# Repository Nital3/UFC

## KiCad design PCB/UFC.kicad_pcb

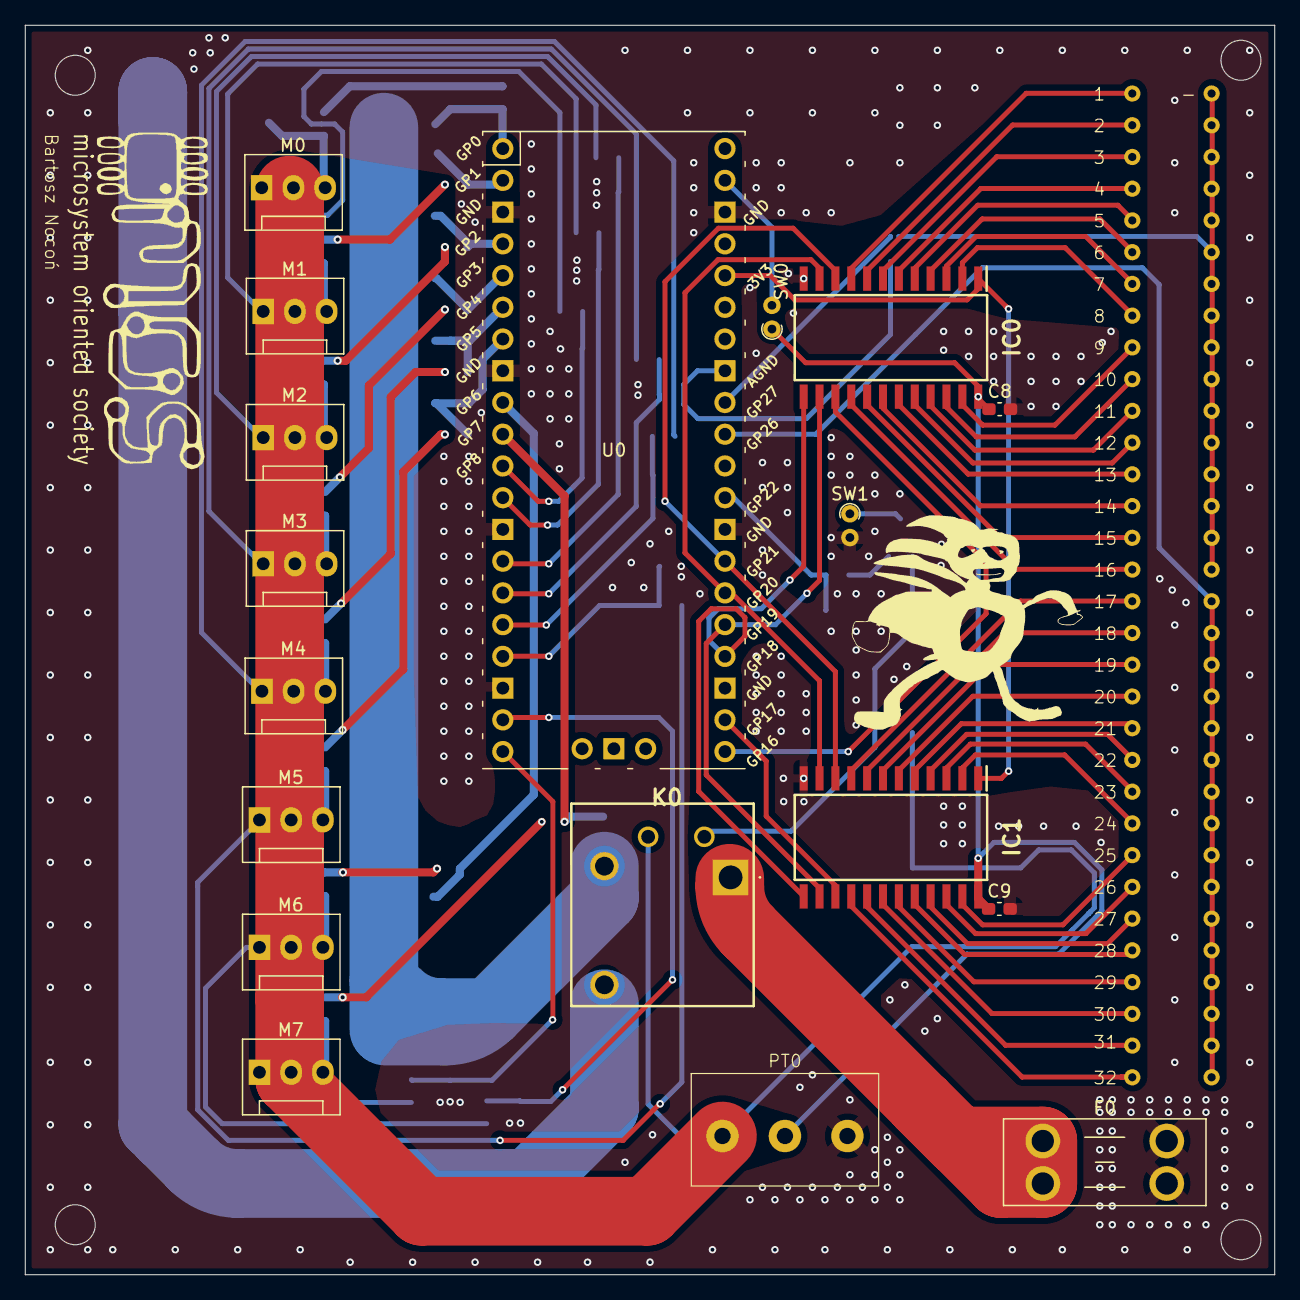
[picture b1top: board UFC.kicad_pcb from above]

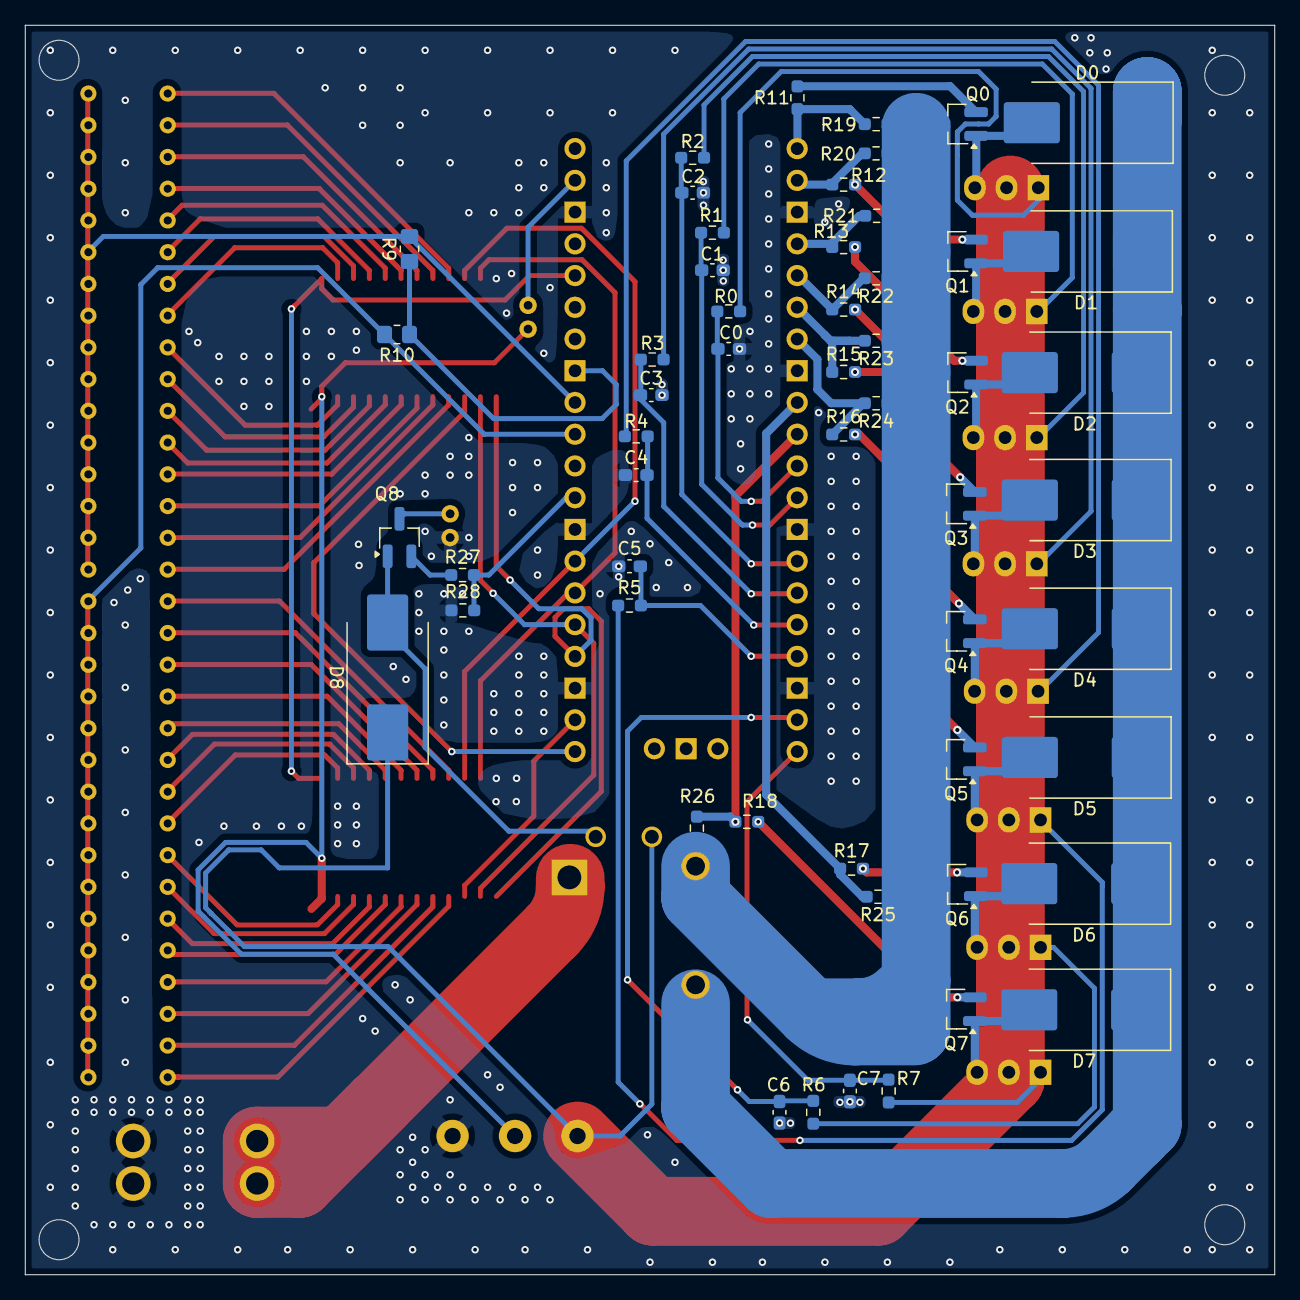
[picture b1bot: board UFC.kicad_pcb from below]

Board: 2 copper layers, 100.0 x 100.0 mm, 73 parts (54 on the bottom side), 85 nets.

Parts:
C0, C1, C2, C3, C4, C5, C6, C7: 4.7u; C_0603_1608Metric_Pad1.08x0.95mm_HandSolder
C8: 1u; C_0603_1608Metric_Pad1.08x0.95mm_HandSolder
C9: C; C_0603_1608Metric_Pad1.08x0.95mm_HandSolder
CONN0: NTC_connector_32x2
D0, D1, D2, D3, D4, D5, D6, D7, D8: D; D_SMC_Handsoldering
F0: Main 12V Fuse; Fuseholder_Blade_Mini_Keystone_3568
IC0, IC1: CD74HCT4067M; SOIC127P1030X265-24N
K0: EP1-3N1S; EP13N1S
M0, M1, M2, M3, M4, M5, M6, M7: Fan_3pin; FanPinHeader_1x03_P2.54mm_Vertical
PT0: Screw_terminal
Q0, Q1, Q2, Q3, Q4, Q5, Q6, Q7, Q8: NMOS; SOT-23_Handsoldering
R0, R1, R2, R3, R4, R5, R6, R7: R300; R_0603_1608Metric_Pad0.98x0.95mm_HandSolder
R9, R10: 10kR; R_0805_2012Metric_Pad1.20x1.40mm_HandSolder
R11, R12, R13, R14, R15, R16, R17, R18, R27: 470R; R_0603_1608Metric_Pad0.98x0.95mm_HandSolder
R19, R20, R21, R22, R23, R24, R25, R26: 4.7KR; R_0603_1608Metric_Pad0.98x0.95mm_HandSolder
R28: R47k; R_0603_1608Metric_Pad0.98x0.95mm_HandSolder
SW0: MCU Reset; R_Axial_DIN0204_L3.6mm_D1.6mm_P1.90mm_Vertical
SW1: Main Power Switch; R_Axial_DIN0204_L3.6mm_D1.6mm_P1.90mm_Vertical
U0: Pico_1; RPi_Pico_TH

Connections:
+5V: C8.1, C9.1, IC0.24 (VCC), IC1.24 (VCC), PT0.2 (5V), SW0.1 (A)
+12V: D8.1 (K), K0.3 (COIL_2), M0.2 (+), M1.2 (+), M2.2 (+), M3.2 (+), M4.2 (+), M5.2 (+), M6.2 (+), M7.2 (+), PT0.1 (12V)
/ADC0: CONN0.17, CONN0.18, CONN0.19, CONN0.20, CONN0.21, CONN0.22, CONN0.23, CONN0.24, CONN0.25, CONN0.26, CONN0.27, CONN0.28, CONN0.29, CONN0.30, CONN0.31, CONN0.32, R9.2, U0.32 (GPIO27_ADC1)
/ADC1: CONN0.49, CONN0.50, CONN0.51, CONN0.52, CONN0.53, CONN0.54, CONN0.55, CONN0.56, CONN0.57, CONN0.58, CONN0.59, CONN0.60, CONN0.61, CONN0.62, CONN0.63, CONN0.64, R10.2, U0.31 (GPIO26_ADC0)
/AGND: R9.1, R10.1, U0.33 (AGND)
/DEMUX 3.3V: IC0.1 (COMMON_INPUT/OUTPUT), IC1.1 (COMMON_INPUT/OUTPUT), U0.36 (3V3)
/DEMUX(0-15)_Disable: IC0.15 (~E), U0.21 (GPIO16)
/DEMUX(16-31)_Disable: IC1.15 (~E), U0.22 (GPIO17)
/DEMUX-Address0: IC0.10 (S0), IC1.10 (S0), U0.27 (GPIO21)
/DEMUX-Address1: IC0.11 (S1), IC1.11 (S1), U0.26 (GPIO20)
/DEMUX-Address2: IC0.14 (S2), IC1.14 (S2), U0.25 (GPIO19)
/DEMUX-Address3: IC0.13 (S3), IC1.13 (S3), U0.24 (GPIO18)
/DEMUX-Thermistor0: CONN0.1, IC0.9 (I0)
/DEMUX-Thermistor1: CONN0.2, IC0.8 (I1)
/DEMUX-Thermistor2: CONN0.3, IC0.7 (I2)
/DEMUX-Thermistor3: CONN0.4, IC0.6 (I3)
/DEMUX-Thermistor4: CONN0.5, IC0.5 (I4)
/DEMUX-Thermistor5: CONN0.6, IC0.4 (I5)
/DEMUX-Thermistor6: CONN0.7, IC0.3 (I6)
/DEMUX-Thermistor7: CONN0.8, IC0.2 (I7)
/DEMUX-Thermistor8: CONN0.9, IC0.23 (I8)
/DEMUX-Thermistor9: CONN0.10, IC0.22 (I9)
/DEMUX-Thermistor10: CONN0.11, IC0.21 (I10)
/DEMUX-Thermistor11: CONN0.12, IC0.20 (I11)
/DEMUX-Thermistor12: CONN0.13, IC0.19 (I12)
/DEMUX-Thermistor13: CONN0.14, IC0.18 (I13)
/DEMUX-Thermistor14: CONN0.15, IC0.17 (I14)
/DEMUX-Thermistor15: CONN0.16, IC0.16 (I15)
/DEMUX-Thermistor16: CONN0.33, IC1.9 (I0)
/DEMUX-Thermistor17: CONN0.34, IC1.8 (I1)
/DEMUX-Thermistor18: CONN0.35, IC1.7 (I2)
/DEMUX-Thermistor19: CONN0.36, IC1.6 (I3)
/DEMUX-Thermistor20: CONN0.37, IC1.5 (I4)
/DEMUX-Thermistor21: CONN0.38, IC1.4 (I5)
/DEMUX-Thermistor22: CONN0.39, IC1.3 (I6)
/DEMUX-Thermistor23: CONN0.40, IC1.2 (I7)
/DEMUX-Thermistor24: CONN0.41, IC1.23 (I8)
/DEMUX-Thermistor25: CONN0.42, IC1.22 (I9)
/DEMUX-Thermistor26: CONN0.43, IC1.21 (I10)
/DEMUX-Thermistor27: CONN0.44, IC1.20 (I11)
/DEMUX-Thermistor28: CONN0.45, IC1.19 (I12)
/DEMUX-Thermistor29: CONN0.46, IC1.18 (I13)
/DEMUX-Thermistor30: CONN0.47, IC1.17 (I14)
/DEMUX-Thermistor31: CONN0.48, IC1.16 (I15)
/NMOS-FAN0: D0.2 (A), Q0.1 (D)
/NMOS-FAN1: D1.2 (A), Q1.1 (D)
/NMOS-FAN2: D2.2 (A), Q2.1 (D)
/NMOS-FAN3: D3.2 (A), Q3.1 (D)
/NMOS-FAN4: D4.2 (A), Q4.1 (D)
/NMOS-FAN5: D5.2 (A), Q5.1 (D)
/NMOS-FAN6: D6.2 (A), Q6.1 (D)
/NMOS-FAN7: D7.2 (A), Q7.1 (D)
/PWM_NMOS0: R11.1, R19.2, U0.1 (GPIO0)
/PWM_NMOS1: R12.1, R20.2, U0.2 (GPIO1)
/PWM_NMOS2: R13.1, R21.2, U0.4 (GPIO2)
/PWM_NMOS3: R14.1, R22.2, U0.5 (GPIO3)
/PWM_NMOS4: R15.1, R23.2, U0.6 (GPIO4)
/PWM_NMOS5: R16.1, R24.2, U0.7 (GPIO5)
/PWM_NMOS6: R17.1, R25.2, U0.9 (GPIO6)
/PWM_NMOS7: R18.1, R26.2, U0.10 (GPIO7)
/Relay_closed: D0.1 (K), D1.1 (K), D2.1 (K), D3.1 (K), D4.1 (K), D5.1 (K), D6.1 (K), D7.1 (K), K0.5 (NC)
/Relay_open: K0.4 (NO), Q0.3 (S), Q1.3 (S), Q2.3 (S), Q3.3 (S), Q4.3 (S), Q5.3 (S), Q6.3 (S), Q7.3 (S), R19.1, R20.1, R21.1, R22.1, R23.1, R24.1, R25.1, R26.1
/Tacho0: C0.2, R0.2, U0.11 (GPIO8)
/Tacho1: C1.2, R1.2, U0.12 (GPIO9)
/Tacho2: C2.2, R2.2, U0.14 (GPIO10)
/Tacho3: C3.2, R3.2, U0.15 (GPIO11)
/Tacho4: C4.2, R4.2, U0.16 (GPIO12)
/Tacho5: C5.2, R5.2, U0.17 (GPIO13)
/Tacho6: C6.2, R6.2, U0.19 (GPIO14)
/Tacho7: C7.2, R7.2, U0.20 (GPIO15)
/Working_indicator: R27.2, R28.1, U0.29 (GPIO22)
GND: C0.1, C1.1, C2.1, C3.1, C4.1, C5.1, C6.1, C7.1, C8.2, C9.2, F0.2, IC0.12 (GND), IC1.12 (GND), PT0.3 (GND), R28.2, SW1.2 (B), U0.3 (GND), U0.8 (GND), U0.13 (GND), U0.18 (GND), U0.23 (GND), U0.28 (GND), U0.38 (GND)
unnamed: D8.2 (A), K0.2 (COIL_1), Q8.1 (D)
unnamed: F0.1, K0.1 (COM)
unnamed: Q0.2 (G), R11.2
unnamed: Q1.2 (G), R12.2
unnamed: Q2.2 (G), R13.2
unnamed: Q3.2 (G), R14.2
unnamed: Q4.2 (G), R15.2
unnamed: Q5.2 (G), R16.2
unnamed: Q6.2 (G), R17.2
unnamed: Q7.2 (G), R18.2
unnamed: Q8.2 (G), R27.1
unnamed: Q8.3 (S), SW1.1 (A)
unnamed: SW0.2 (B), U0.39 (VSYS)

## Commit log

2024-10-26 Test
2024-10-27 Add safe relay discharge diode
    Add safe relay discharge diode, clean up testing wires
2024-10-27 Tweak relay circuit
2024-11-01 File Reorganisation
    Put PCB project files into PCB/ folder
2024-11-01 Setup C project
    Set up files for coding in C
2024-11-09 Add basic HTML server Interface
    Add blueprint HTML web server functionality for data display and controls
2024-11-09 Test CSS
    Test if basic CSS functionality works
2024-11-20 Scheme circuit placement change
2024-11-20 Create symbol lib, add demux symbol
2024-11-20 Add thermistor switch prototype
2024-11-20 Thermistor update
2024-11-20 Finished demux prototype
2024-11-21 Relay polishing
2024-11-21 tacho
2024-11-21 Revert "Update UFC.kicad_sch"
    This reverts commit 1db8f7cdeda4f3192a7a983fd2073eb96bcbd704.
2024-11-30 test tacho fan branch
2024-11-30 Tests
2024-11-30 Description fix
2024-12-12 WIP
    Work in progress
2025-02-18 footprinty machen
2025-03-23 chuj
2025-03-23 footprinty dokonczon
    w końcu xd
2025-03-23 footprinty dokonczon, ale teraz tak na serio
2025-03-27 pcb machen
    do oceny
2025-04-03 nigger
    nigger ugly ass\
2025-04-09 drobny update
2025-04-10 nearly done
2025-04-10 pcb update
    finished probably
2025-04-10 zone done
2025-04-11 silkscreen machen
2025-04-12 wiecej oznaczen
